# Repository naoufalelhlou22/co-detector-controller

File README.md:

# Smart Dual Gas Detector (CO + LPG) Controller

[-brightgreen.svg)]()

Production-grade, 4-layer smart dual-gas detector hardware platform designed around the **ESP32-C3** Wi-Fi/BLE microcontroller. Integrates precision analog front-ends for simultaneous monitoring of **Carbon Monoxide (CO)** and **Combustible Liquefied Petroleum Gas (LPG)**.

> [!TIP]
> Ready-to-manufacture Gerbers, schematic PDF, BOM, and CPL files are attached directly to the [v2.0.0 Release](https://github.com/naoufalelhlou22/co-detector-controller/releases/tag/v2.0.0).

---

## Features

- **Microcontroller:** ESP32-C3-MINI-1 (RISC-V 32-bit single-core, Wi-Fi 4 + Bluetooth 5 LE).
- **Carbon Monoxide Subsystem (Zone D):**
  - Sensor: **Winsen ME3-CO** (electrochemical cell).
  - Analog Front-End: **TI LMP91000** configurable AFE potentiostat with programmable transimpedance gain (TIA) via $I^2C$.
- **Combustible / LPG Subsystem (Zone F):**
  - Sensor: **Figaro TGS2610-C00** (metal-oxide semiconductor gas sensor).
  - High-side PWM-modulated heater driver and buffered voltage divider analog readout.
- **Power Management (Zone A):**
  - Primary Input: 5V DC via USB-C or screw terminals.
  - 3.3V Step-Down: Low-noise, high-efficiency LDO / buck regulator.
  - Active reverse-polarity, over-voltage, and transient protection.
- **User Interface & Annunciation (Zone C):**
  - Audio: Piezo sounder with transistor buffer for audible emergency alarms.
  - Visual: Status and alarm LEDs (Power, CO Alert, LPG Alert, Fault/WiFi).
  - Input: Tactile switches for Alarm Mute/Hush and Self-Test.
- **Fabrication & Assembly:**
  - 100% single-sided SMT placement (Top side only) for cost-effective PCBA.
  - Verified LCSC part numbers for turn-key assembly via JLCPCB.

---

## Hardware Specifications

| Parameter | Specification |
| :--- | :--- |
| **Dimensions** | 70.0 mm × 50.0 mm |
| **Layer Count** | 4 Layers (Signal Top - GND - 3V3/Power - Signal Bottom) |
| **PCB Thickness** | 1.6 mm |
| **Surface Finish** | ENIG (Electroless Nickel Immersion Gold) recommended |
| **Copper Weight** | 1 oz outer / 1 oz inner |
| **Sensors Installed** | Winsen ME3-CO (CO), Figaro TGS2610 (LPG) |
| **Target Standards** | Designed referencing UL 2034 / EN 50291 acoustic and sensitivity curves |

---

## Repository Structure

```
co_detector_controller/
├── co_detector_controller.kicad_pro    # KiCad 10 project file
├── co_detector_controller.kicad_sch    # Main schematic
├── co_detector_controller.kicad_pcb    # 4-layer routed PCB layout
├── co_detector_symbols.kicad_sym       # Project custom symbol library
├── sym-lib-table                       # Symbol library mapping
├── fp-lib-table                        # Footprint library mapping
├── custom_lib.pretty/                  # Custom footprints with verified courtyards
├── co_detector_controller_schematic.pdf# High-resolution PDF schematic export
├── README_JLCPCB.md                    # Complete JLCPCB PCBA ordering guide
│
├── fab_jlcpcb/                         # Ready-to-order manufacturing deliverables
│   ├── co_detector_controller_gerbers_jlcpcb.zip # Gerber & Excellon drill archive
│   ├── JLCPCB_BOM.csv                  # Bill of Materials mapped with LCSC part numbers
│   ├── JLCPCB_CPL.csv                  # Centroid / Pick & Place coordinates
│   └── gerbers/                        # Extracted RS-274X layer files
│
├── reports/                            # Automated verification logs
│   ├── drc_stage5.json                 # Design Rules Check report (0 errors, 0 unconnected)
│   ├── erc_report.json                 # Electrical Rules Check report (0 errors)
│   ├── stage5_net_stats.json           # Track, via, and copper plane metrics
│   └── BOM_engineering_master.csv      # Detailed engineering BOM
│
├── audit_rev3/                         # Simulation and firmware verification
│   ├── spice/                          # SPICE netlists and simulation run results
│   ├── run_all_spice_sims.py           # Automated ngspice test runner
│   └── wokwi/                          # Wokwi firmware simulation testbench
│       ├── src/                        # Embedded C++ drivers (pins, power, watchdog)
│       └── test/                       # 18-scenario automated verification testbench
│
├── scripts/                            # KiCad Python automation scripts
│   ├── build_all.py                    # Master pipeline runner (rebuilds entire PCBA from scratch)
│   ├── build_stage4.py                 # Automated PCB placement & routing engine
│   ├── generate_schematic.py           # Schematic & netlist generator
│   ├── build_custom_fps.py             # Custom footprint generator
│   ├── build_3d_models.py              # 3D mechanical model export tool
│   ├── verify_stage5.py                # Automated KiCad DRC & netclass verification
│   ├── build_jlcpcb_package.py         # Gerber, drill, and zip packager
│   ├── update_jlcpcb_bom_cpl.py        # 100% matched BOM & CPL parity builder
│   └── calculate_pcba_costs.py         # JLCPCB assembly cost estimator
│
└── 3dmodels/                           # 3D CAD models (VRML / STEP)
```

---

## Manufacturing & Assembly

For complete step-by-step instructions on ordering boards and PCBA through JLCPCB, see the [JLCPCB Ordering Guide](README_JLCPCB.md).

> [!CAUTION]
> Chemical gas sensors (**Winsen ME3-CO** and **Figaro TGS2610**) must **NOT** be passed through the SMT reflow oven. Solder sockets or hand-solder sensors post-reflow.

---

## License

This project is open-source hardware licensed under the [MIT License](LICENSE) (or CERN-OHL-P / user preferred license).

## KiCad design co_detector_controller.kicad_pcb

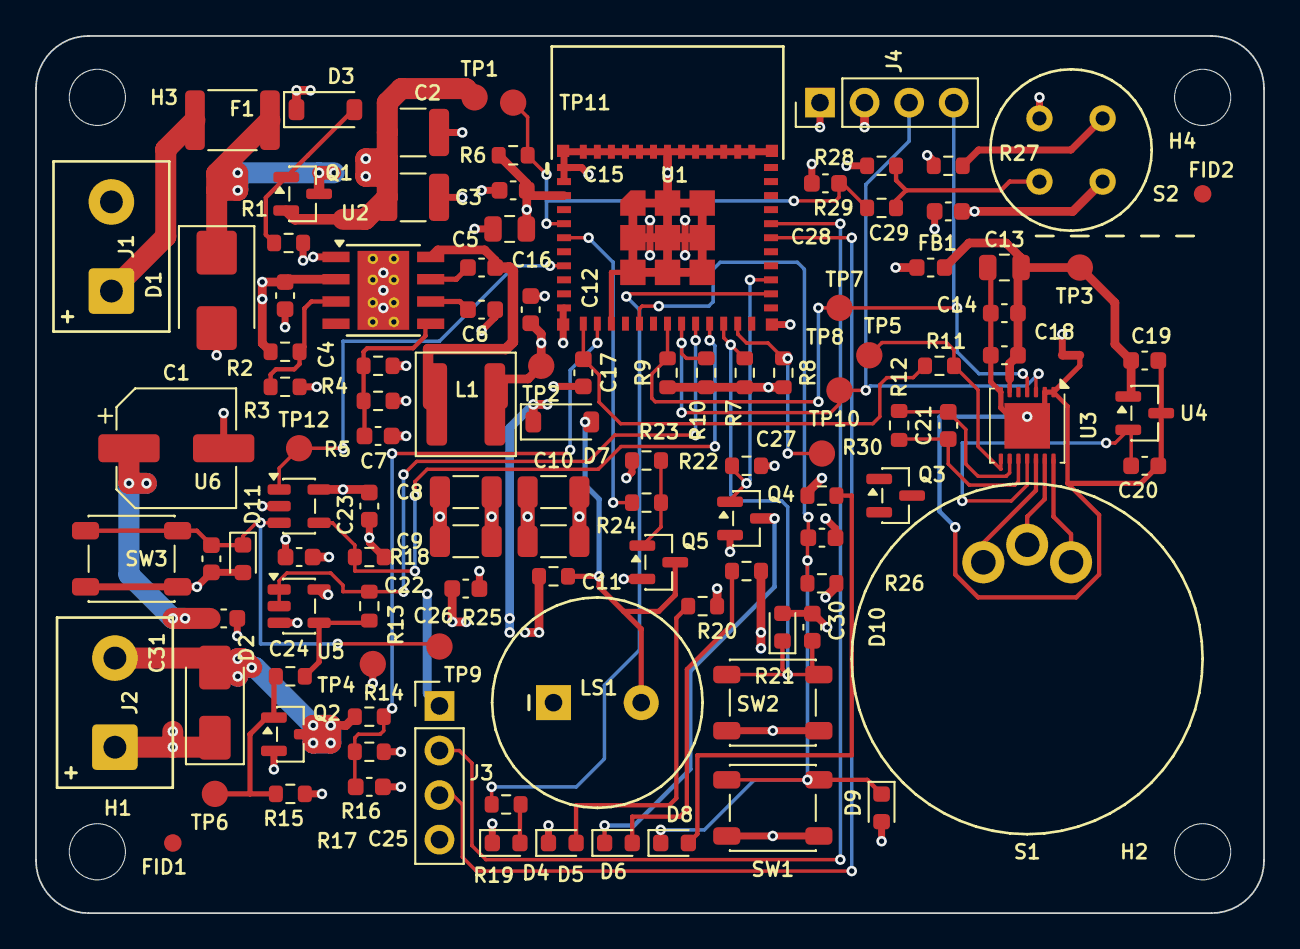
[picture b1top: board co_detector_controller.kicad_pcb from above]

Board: 4 copper layers, 70.0 x 50.0 mm, 115 parts (0 on the bottom side), 49 nets.

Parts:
C1: 47uF_35V; CP_Elec_6.3x7.7
C2, C3: 10uF_50V; C_1210_3225Metric
C4, C5, C12, C14, C16, C17, C18, C19, C20, C22, C23, C25, C27, C28, C29, C30, C31: 100nF; C_0603_1608Metric
C6, C21: 1uF; C_0603_1608Metric
C7: DNP; C_0603_1608Metric
C8, C9, C10, C11: 22uF_10V; C_1206_3216Metric
C13, C15: 10uF_10V; C_0805_2012Metric
C24, C26: 100nF_50V; C_0603_1608Metric
D1: SMBJ15CA; D_SMB
D2: B240A; D_SMA
D3: BZT52C15; D_SOD-123
D4: RED_ALARM; LED_0603_1608Metric
D5: GRN_OK; LED_0603_1608Metric
D6: BLU_WIFI; LED_0603_1608Metric
D7: 1N4148W; D_SOD-123
D8: YLW_FAULT; LED_0603_1608Metric
D9, D10, D11: TVS_3V3_ESD; D_0603_1608Metric
F1: 1.5A_PTC; Fuse_1812_4532Metric
FB1: 220R_100MHz; L_0603_1608Metric
FID1: FID_BL; Fiducial_1mm_Mask2mm
FID2: FID_TR; Fiducial_1mm_Mask2mm
H1, H2, H3, H4: M3_NPTH; MountingHole_3.2mm_M3
J1: 12V_IN; TerminalBlock_Phoenix_MKDS-1,5-2-5.08_1x02_P5.08mm_Horizont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
J2: EXT_ALARM_12V; TerminalBlock_Phoenix_MKDS-1,5-2-5.08_1x02_P5.08mm_Horizont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
J3: UART_HDR; PinHeader_1x04_P2.54mm_Vertical
J4: OLED_I2C; PinHeader_1x04_P2.54mm_Vertical
L1: 6.8uH; L_Coilcraft_XAL5030-XXX
LS1: PS1240_OR_SPKR; Buzzer_TDK_PS1240P02BT_D12.2mm_H6.5mm
NT1: NetTie_AGND_GND; NetTie-2_SMD_Pad0.5mm
Q1: AO3407A; SOT-23
Q2: IRLML6344; SOT-23
Q3: MMBFJ177_DNP; SOT-23
Q4: 2N7002; SOT-23
Q5: AO3400A; SOT-23
R1, R7, R8, R13, R24, R26: 10k; R_0603_1608Metric
R2, R4, R15, R16, R22: 100k; R_0603_1608Metric
R3, R12, R18: DNP; R_0603_1608Metric
R5: 43.2k; R_0603_1608Metric
R6: 10k_DNP; R_0603_1608Metric
R9, R10, R28: 4.7k; R_0603_1608Metric
R11, R29: 1k; R_0603_1608Metric
R14, R23: 100R; R_0603_1608Metric
R17: 15k; R_0603_1608Metric
R19: 270R; R_0603_1608Metric
R20, R30: 330R; R_0603_1608Metric
R21, R25: 2.2k; R_0603_1608Metric
R27: 0R_OR_5V; R_0603_1608Metric
S1: ME3-CO; TestPoint_Pad_D1.5mm
S2: TGS2610-C00; TestPoint_Pad_D1.5mm
SW1: TEST_SELF_CHECK; SW_SPST_PTS647_Sx50
SW2: HUSH_OLED; SW_SPST_PTS647_Sx50
SW3: HW_MASTER_RST; SW_SPST_PTS647_Sx50
TP1: +12V; TestPoint_Pad_D1.5mm
TP2: +3V3; TestPoint_Pad_D1.5mm
TP3: AVDD; TestPoint_Pad_D1.5mm
TP4: GND; TestPoint_Pad_D1.5mm
TP5: VOUT; TestPoint_Pad_D1.5mm
TP6: VALVE_GATE; TestPoint_Pad_D1.5mm
TP7: I2C_SDA; TestPoint_Pad_D1.5mm
TP8: I2C_SCL; TestPoint_Pad_D1.5mm
TP9: EN_PAD; TestPoint_Pad_D1.5mm
TP10: BOOT_PAD; TestPoint_Pad_D1.5mm
TP11: LPG_ADC; TestPoint_Pad_D1.5mm
TP12: NRST; TestPoint_Pad_D1.5mm
U1: ESP32-C3-MINI-1; ESP32-C6-MINI-1
U2: LMR33620ADDAR; TI_SO-PowerPAD-8_ThermalVias
U3: LMP91000SDE; WSON-14-1EP_4.0x4.0mm_P0.5mm_EP2.6x2.6mm
U4: REF3325; SOT-23
U5: 74LVC1G08; SOT-23-5
U6: TPS3823-33; SOT-23-5

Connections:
+3V3: C7.2, C8.1, C9.1, C10.1, C11.1, C12.1, C15.2, C16.2, C22.2, C23.2, C29.1, FB1.1, J3.1, J4.2, L1.2, R4.2, R6.1, R7.1, R8.1, R9.1, R10.1, R20.2, R26.2, R27.1, R30.1, S2.3, TP2.1, U1.3, U5.5, U6.5
+12V: C1.1, C2.1, C3.1, C4.1, C24.1, C26.1, D2.1, D3.1, D7.1, J2.1, LS1.1, Q1.2, R2.1, R21.1, R25.1, TP1.1, U2.2
+12V_F: D1.1, F1.2, Q1.3
+12V_IN: F1.1, J1.1
AGND: C13.1, C14.1, C18.1, C19.2, C20.2, NT1.2, U3.1, U3.2, U3.7, U3.15, U4.3
AVDD: C13.2, C14.2, C18.2, C19.1, FB1.2, TP3.1, U3.6, U4.1
BLU_A: D6.2, R21.2
BLU_K: D6.1, Q4.3
BOOT_N: R8.2, TP10.1, U1.23
BUCK_BOOT: C5.1, U2.7
BUCK_EN: R2.2, R3.1, U2.3
BUCK_FB: C7.1, R4.1, R5.1, U2.5
BUCK_SW: C5.2, L1.1, U2.8
BUCK_VCC: C6.1, U2.6
BUZZER: R23.1, U1.6
BUZ_B: Q5.1, R23.2, R24.1
BUZ_K: D7.2, LS1.2, Q5.3, R25.2
CE: S1.3, U3.14
GND: C1.2, C2.2, C3.2, C4.2, C6.2, C8.2, C9.2, C10.2, C11.2, C12.2, C15.1, C16.1, C17.2, C22.1, C23.1, C24.2, C25.2, C26.2, C27.2, C28.1, C29.2, C30.2, C31.1, D1.2, D4.1, D5.1, D9.2, D10.2, D11.2, J1.2, J3.4, J4.1, NT1.1, Q2.2, Q4.2, Q5.2, R1.2, R3.2, R5.2, R15.2, R17.2, R18.2, R22.2, R24.2, R28.2, S2.1, SW1.2, SW2.2, SW3.2, TP4.1, U1.1, U1.2, U1.11, U1.14, U1.36, U1.37, U1.38, U1.39, U1.40, U1.41, U1.42, U1.43, U1.44, U1.45, U1.46, U1.47, U1.48, U1.49, U1.50, U1.51, U1.52, U1.53, U2.1, U2.9, U5.3, U6.2
GRN_A: D5.2, R20.1
HUSH_N: C30.1, D10.1, R7.2, SW2.1, U1.22
I2C_SCL: J4.3, R10.2, TP8.1, U1.19, U3.3
I2C_SDA: J4.4, R9.2, TP7.1, U1.18, U3.4
LED_BLU: Q4.1, R22.1, U1.27
LED_RED: R19.1, U1.26
LPG_ADC: C28.2, R6.2, R29.2, TP11.1, U1.5
LPG_HTR: R27.2, S2.4
LPG_SNS: R28.1, R29.1, S2.2
MR_N: C31.2, D11.1, SW3.1, TP9.1, U6.3
NRST: TP12.1, U1.8, U6.1
Q1_G: D3.2, Q1.1, R1.1
RE: S1.2, U3.13
RED_A: D4.2, R19.2
TEST_N: C27.1, D8.1, D9.1, R26.1, SW1.1, U1.16
TIA_C1: C21.1, R12.1, U3.10
TIA_C2: C21.2, R12.2, U3.9
UART_RX: J3.3, U1.30
UART_TX: J3.2, U1.31
VALVE_DRV: R13.1, R14.2, U5.4
VALVE_EN: R13.2, U1.20, U5.1, U5.2
VALVE_GATE: Q2.1, R14.1, R15.1, TP6.1
VALVE_NEG: D2.2, J2.2, Q2.3, R16.1
VALVE_SENSE: C25.1, R16.2, R17.1, U1.13
VOUT: R11.2, TP5.1, U3.8
VOUT_ADC: C17.1, R11.1, U1.12
VREF: C20.1, U3.11, U4.2
WDI: R18.1, U1.21, U6.4
WE: S1.1, U3.12
YLW_A: D8.2, R30.2

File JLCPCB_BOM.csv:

Comment,Designator,Footprint,LCSC Part #
100nF 50V X7R,"C4,C5,C12,C14,C16,C17,C18,C19,C20,C22,C23,C24,C25,C26,C27,C28,C29,C30,C31",0603,C14663
1uF 16V X7R,"C6,C21",0603,C15849
10uF 10V X7R,"C13,C15",0805,C15850
22uF 25V X5R,"C8,C9,C10,C11",1206,C159045
10uF 50V X7R,"C2,C3",1210,
47uF 35V SMD Electrolytic,C1,SMD-6.3x7.7,
10k 1%,"R1,R7,R8,R13,R24,R26",0603,C25804
100k 1%,"R2,R4,R15,R16,R22",0603,C25803
4.7k 1%,"R9,R10,R28",0603,C23162
1k 1%,"R11,R29",0603,C22548
100R 1%,"R14,R23",0603,C22775
15k 1%,R17,0603,C22809
270R 1%,R19,0603,C22966
330R 1%,"R20,R30",0603,C23138
2.2k 1%,"R21,R25",0603,C4190
0R Jumper,R27,0603,C21189
43.2k 1%,R5,0603,C2930102
1N4148W,D7,SOD-123,C81598
Red LED 0603,D4,0603,C434419
Green LED 0603,D5,0603,C965805
Blue LED 0603,D6,0603,C2986058
Yellow LED 0603,D8,0603,C965805
SS24 Schottky 40V 2A,D2,SMA,C2887543
SMBJ15CA TVS 15V,D1,SMB,C135047
BZT52C15 15V Zener,D3,SOD-123,C2104
ESD TVS 3.3V,"D9,D10,D11",0603,C15975
ESP32-C3-MINI-1-N4,U1,ESP32-C3-MINI-1,C2838502
LMR33620ADDAR,U2,SOIC-8-1EP,C2071694
REF3325AIDBZR,U4,SOT-23,C69039
SN74LVC1G08DBVR,U5,SOT-23-5,C434068
TPS3823-33DBVR,U6,SOT-23-5,C7719
LMP91000SDE/NOPB,U3,WSON-14-1EP,C181364
AO3407A,Q1,SOT-23,C181093
AO3400A,"Q2,Q5",SOT-23,C20917
2N7002,Q4,SOT-23,C8545
TS-1187A Tact Switch,"SW1,SW2,SW3",PTS647,C318884
Ferrite Bead 220R,FB1,0603,C139160
PTC Fuse 1.5A 24V,F1,1812,C209713
6.8uH Power Inductor,L1,5040_5030,C495812
5.08mm 2P Terminal Block,"J1,J2",5.08mm-2P,C8465
Pin Header 1x4 2.54mm,"J3,J4",2.54mm-1x4,C2255
Buzzer 12V 85dB,LS1,PS1240P02BT,C96465

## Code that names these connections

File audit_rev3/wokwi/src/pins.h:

// pins.h — GPIO map taken verbatim from the Rev2 KiCad netlist export
// (audit_rev3/netlist/connectivity.txt, symbol U1 ESP32-C3-MINI-1).
#pragma once

namespace pins {
constexpr int VOUT_ADC    = 0;   // U1.12  ADC1_CH0  <- LMP91000 VOUT via R11/C17
constexpr int VALVE_SENSE = 1;   // U1.13  ADC1_CH1  <- J2 continuity divider R16/R17
constexpr int LPG_ADC     = 2;   // U1.5   ADC1_CH2  <- TGS2610 divider  (STRAPPING PIN! see audit H-02)
constexpr int BUZZER      = 3;   // U1.6   -> R23 -> Q5 gate (LS1)
constexpr int I2C_SDA     = 4;   // U1.18  OLED J4 + LMP91000 (0x48)
constexpr int I2C_SCL     = 5;   // U1.19
constexpr int VALVE_EN    = 6;   // U1.20  -> U5 A=B (bus-hold latch with R13) -> Q2 -> J2
constexpr int WDI         = 7;   // U1.21  -> TPS3823 WDI (watchdog ACTIVE once driven)
constexpr int HUSH_N      = 8;   // U1.22  SW2, R7 pull-up (strapping pin, high = OK)
constexpr int BOOT_N      = 9;   // U1.23  TP10 service pad only
constexpr int TEST_N_D8   = 10;  // U1.16  SW1 to GND  AND  D8 (yellow) cathode -> OPEN-DRAIN ONLY
constexpr int LED_RED     = 18;  // U1.26  D4 via R19 (USB D-; no USB used on this board)
constexpr int LED_BLU     = 19;  // U1.27  Q4 -> D6 (USB D+; ROM enables D+ pull-up at boot -> D6 glows until init)
// GPIO20/21 = UART0 on J3. LMP91000 MENB is hard-wired to AGND (always enabled) - no GPIO.
}  // namespace pins

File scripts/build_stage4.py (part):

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add_track_poly("BUZ_K", F_Cu, 0.3, chain_45((32.1, 19.2), (32.1, 18.6), (33.5, 17.2, "diag"), (34.5, 16.2, "diag"), (34.5, 12.0)))
add_track_poly("BUZ_K", F_Cu, 0.3, chain_45((33.5, 17.2), (35.5, 17.2), (36.438, 18.138, "diag"), (36.438, 20.0)))

# 5.3 LED_RED & RED_A (U1.26 GPIO18@(41.9, 35.3) -> R19.1@(25.975, 6.2))
add_track_poly("RED_A", F_Cu, 0.25, chain_45((27.625, 6.2), (27.588, 6.163, "diag"), (27.588, 4.0)))
add_track_poly("LED_RED", F_Cu, 0.2, chain_45((41.9, 35.3), (33.8, 35.3), (33.65, 35.15, "diag")))
add_via("LED_RED", 33.65, 35.15)
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add_via("LED_RED", 25.975, 7.2)
add_track_poly("LED_RED", F_Cu, 0.2, [(25.975, 7.2), (25.975, 6.2)])

# 5.4 GRN_A & HUSH_N (U1.22 GPIO8@(39.2, 33.6) -> R7.2@(40.4, 31.625) -> D10.1@(42.55, 15.5125) & C30.1@(44.25, 15.525) -> SW2.1@(39.375, 13.6) & (44.625, 13.6))
add_track_poly("GRN_A", F_Cu, 0.25, chain_45((37.175, 17.5), (36.5, 16.825, "diag"), (36.5, 6.55), (36.1, 6.15, "diag"), (30.788, 6.15), (30.788, 4.0)))
add_track_poly("HUSH_N", F_Cu, 0.2, chain_45((39.2, 33.6), (39.2, 32.8), (39.6, 32.4, "diag"), (40.375, 31.625), (40.4, 31.625)))
add_via("HUSH_N", 39.6, 32.4)
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add_track_poly("LED_BLU", F_Cu, 0.2, chain_45((40.5, 24.5), (39.675, 25.325, "diag"), (39.675, 25.5)))
add_track_poly("LED_BLU", F_Cu, 0.2, chain_45((40.5, 24.5), (39.562, 23.562, "diag"), (39.562, 23.45)))

# 5.6 BOOT_N (Dedicated Service Boot Pad ONLY: U1.23 GPIO9@(40.0, 33.6) -> R8.2@(42.6, 31.625) -> TP10.1@(44.8, 26.2))
add_track_poly("BOOT_N", F_Cu, 0.2, chain_45((40.0, 33.6), (40.0, 33.0), (40.5, 32.5), (41.725, 32.5), (42.6, 31.625), (42.85, 31.625)))
add_via("BOOT_N", 42.85, 31.625)
add_track_poly("BOOT_N", B_Cu, 0.2, [(42.85, 31.625), (42.85, 26.2)])
add_via("BOOT_N", 42.85, 26.2)
add_track_poly("BOOT_N", F_Cu, 0.2, [(42.85, 26.2), (44.8, 26.2)])

# 5.7 TEST_N & YLW_A (U1.16 GPIO10@(34.4, 33.6) -> C27.1@(44.025, 21.4) -> R26.1@(43.975, 18.8) -> SW1.1@(39.375, 7.6) & (44.625, 7.6) -> D9.1@(48.2, 6.7875) -> D8.1@(35.612, 4.0)):
# YLW_A: R30.2@(45.625, 23.8) -> F.Cu x=46.50 -> y=9.0 corridor -> x=37.70 -> D8.2@(37.188, 4.0) (0 vias!)
add_track_poly("YLW_A", F_Cu, 0.25, chain_45((45.625, 23.8), (46.5, 23.8), (46.5, 9.0), (37.7, 9.0), (37.7, 4.512), (37.188, 4.0, "diag")))

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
